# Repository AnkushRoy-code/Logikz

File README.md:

# Logikz

I designed a simple circuit board that can function as three different logic
gates:- `AND`, `OR`, and `NOR`

<p align="center">
  <br>
</p>

### Making of Logikz
This is my third PCB and this time around I wanted to know how transistors
work, and also wanted to know how logic gates work. I myself implemented the
`AND` and `OR` gates but had to look up how to do a `NOR` gate. Later I also
changed how my `OR` gate works looking at the implementation of `NOR` gate.

The first iteration would've never worked, because of absolutely no current
calculations done. Used [circuit.js](https://www.falstad.com/circuit/circuitjs.html) to fix my implementation.
Earlier it had like 5 buttons, two for `A` and `B` inputs and the rset for
choosing between the gates. But had to ditch that idea because current it
didn't work in the simulation. Now I have 9 buttons, `A` and `B` for each
gates, so total 3 `A` and 3 `B` input buttons.

Reason why the first iteration didn't work: It had something to do with
"current takes the least resistive path", it is hard to explain in text.

The simulation file is present in `~/logikz_circuitjs.txt`, you can click [this](https://www.falstad.com/circuit/circuitjs.html?ctz=CQAgjCAMB0l3BWcMBMcUHYMGZIA4UA2ATmIxAQiQUgoFMBaMMAKADdxiUQUUAWTtzCFaokH1rYo0mAhYB3QeBFLCAyAtUDM3NVE06Qew8UL6ATjwzdTIbHgG3afDHAPWQTFdgTcvozR8-PjxnbGDQ-UUgz2Ewvzj9AGdxcM8Q2gQMMwYM6QgAMwBDABskuhYUvjT-CmzYlVpC0vLKu0I8BoowBLMmkGKyioAXEBwzPXG7IXBPFGhCbHtIGn5+SEIRbEYEKXnF5dW+dYQ8HB2IMDgQABM6YoBXEuHAhxBbewE9DWi3vWrdOpXo4zJ9wChOj87G8ep0AeDIW14XoEHwvupZoNWlU0rCKGiEfkBi0KpZKL0jPwurReFDrLQGGlQgy0nS0J40vTplEQMyOdw+azNKj0WNsBMgYoML5udlOkKpR1ZUq0IjFGAuDwqRruIYoTqrNw5YaecbVWMVR4NKM8MIjAJbaCZhAGPslqEjus+L5CDs9gt3StIGsJKdiHwLshaHdHs9NI77by7cxuFCRYSE3ioZmIUmzCmeXg0ky9AreaWBXoDdmq5q8MYrfGG0bLan49dGTYevyecRu53wGBxT39UOcrix3MqRphEJJ67tSgarxtLd7kUnsMGCU6DdZmIYJBWOql34V+C0nrND1Lx569pG6NpQlu8+Gv0IBhoDfxWAEKQ4BCRYdmIcBoGOPhCGsJZhFcAEUB2TormjddNxYG07SYbsE1qS45mgGgEEIIjgz4UhhE2BAQJ4aAUFRShiNMao-xQYhqOQtdYxeRVOlqPlajTepaimASWEsQwGA+JVJL6cRXChcVeILPhMILBTpMiFSckiDQqlU7t0yw1NMRJJFMMiQydJMoZNGInICxEtT4xqRIriI98eTc+yVC8qdJWQdyFwEZhhyCnkJMSCSYg0cSPEZGVFI5GVnHk9TeJiRLGTeNKku4TLwgCaJpIK8QOxKnKsoECQWWypEyrePJKqJLEKiqMr2Ua8rrNaMkCQYSI7M8KyXDcXqBCMoxArUuS3CfUKljMESwTwphoGwOUsnCbAh0oVw8EYPRXVgf8fB6VF62EIiIwYKtrhjDc41GKC-AWow4uW2YwHAosOn4ERMDIjpfRunJCAWbIsiuDAbxwU4qJupAOPutDFE6t5-xe2rFAxjl0c1RlhzTfHXuejlCc0Tr2SW9k6Xmqn5vJ7GhLyQgqVyHTbLZsFBqaqFWfGvI4PSDmpUgcawS5XnbLwdK-hl9IyzfJqlfhPn5dyTkZQ1tspS1+ErjZ1Xr1IhWhBWHIjfVc3TYC8clRi22OSVXywppNBAmku0Ir6dxARNMt+a6UmvB5YPOXZAc6S1hzQqcxRvZpOKnF9zxbAkkIeUyqSlO7Crs6GwrJu02gcJFvMC-Lia+fe3Q4rtKF086b3wrrsxDADw2Bq5rGxjF3GBCF9nC6imVG+HuK8hiIf9CAA) link to see my project in action.

### PCB

<table>
  <tr>
    <td align="center">
      <br>
      <b>Front Of the PCB</b>
    </td>
    <td align="center">
      <br>
      <b>Back Of the PCB</b>
    </td>
    <td align="center">
      <br>
      <b>Back of the PCB without Silkscreen</b>
    </td>
  </tr>
  <tr>
    <td align="center">
      <br>
      <b>Front Of the PCB (3D)</b>
    </td>
    <td align="center">
      <br>
      <b>Back Of the PCB (3D)</b>
    </td>
    <td align="center">
      <br>
      <b>Simulation in CircuitJS</b>
    </td>
  </tr>
</table>

### SChematic
<p align="center">
  <br>
</p>

### BOM
`~/BOM.csv` has BOM of this project.

| QTY            | Name              |
| -------------- | ---------------   |
| 1              | Battery Holder    |
| 1              | LED               |
| 6              | NPN Transistor    |
| 2              | 220 Ohm Resistor  |
| 5              | 4.7k Ohm Resistor |
| 9              | Push Button       |

Made by `@Ankush Roy` in Slack from Hack Club

Made as a part of https://solder.hackclub.com/!

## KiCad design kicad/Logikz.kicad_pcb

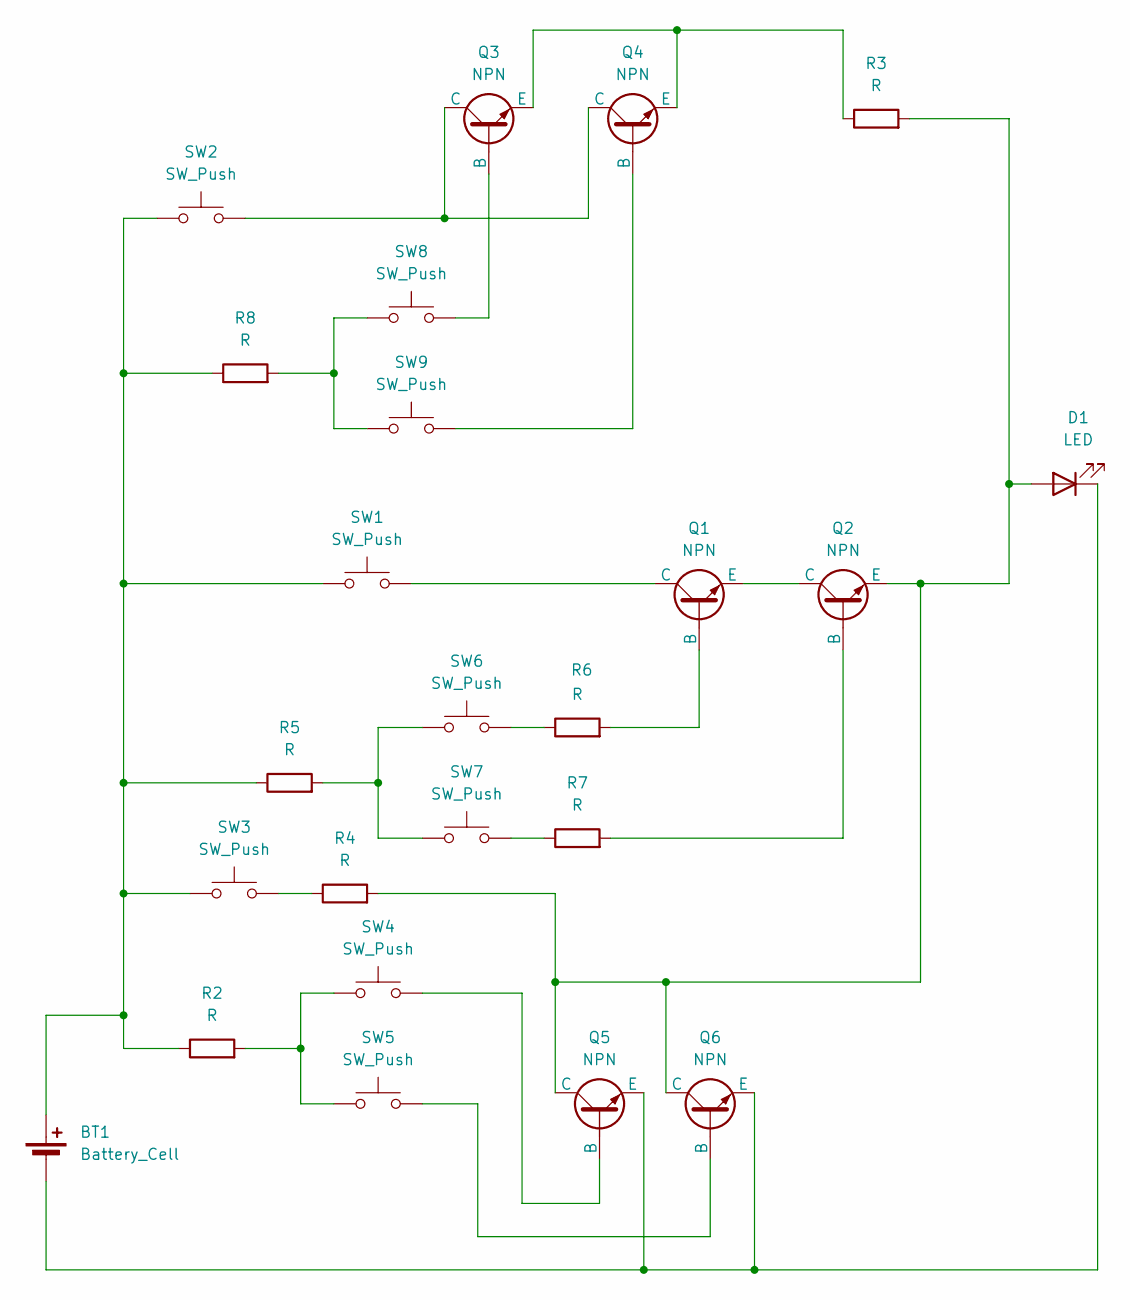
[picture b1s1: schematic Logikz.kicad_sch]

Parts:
BT1: Battery_Cell; BatteryHolder_Keystone_3034_1x20mm
D1: LED; LED_D5.0mm
Q1, Q2, Q3, Q4, Q5, Q6: NPN; TO-92L_HandSolder
R2, R3, R4, R5, R6, R7, R8: R; R_Axial_DIN0207_L6.3mm_D2.5mm_P7.62mm_Horizontal
SW1, SW2, SW3, SW4, SW5, SW6, SW7, SW8, SW9: SW_Push; SW_PUSH_6mm

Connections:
unnamed: BT1.1 (+), R2.1, R5.1, R8.1, SW1.1, SW2.1, SW3.1
unnamed: BT1.2 (-), D1.1 (K), Q5.3 (E), Q6.3 (E)
unnamed: D1.2 (A), Q2.3 (E), Q5.1 (C), Q6.1 (C), R3.2, R4.2
unnamed: Q1.2 (B), R6.2
unnamed: Q1.1 (C), SW1.2
unnamed: Q1.3 (E), Q2.1 (C)
unnamed: Q2.2 (B), R7.2
unnamed: Q3.2 (B), SW8.2
unnamed: Q3.1 (C), Q4.1 (C), SW2.2
unnamed: Q3.3 (E), Q4.3 (E), R3.1
unnamed: Q4.2 (B), SW9.2
unnamed: Q5.2 (B), SW4.2
unnamed: Q6.2 (B), SW5.2
unnamed: R2.2, SW4.1, SW5.1
unnamed: R4.1, SW3.2
unnamed: R5.2, SW6.1, SW7.1
unnamed: R6.1, SW6.2
unnamed: R7.1, SW7.2
unnamed: R8.2, SW8.1, SW9.1

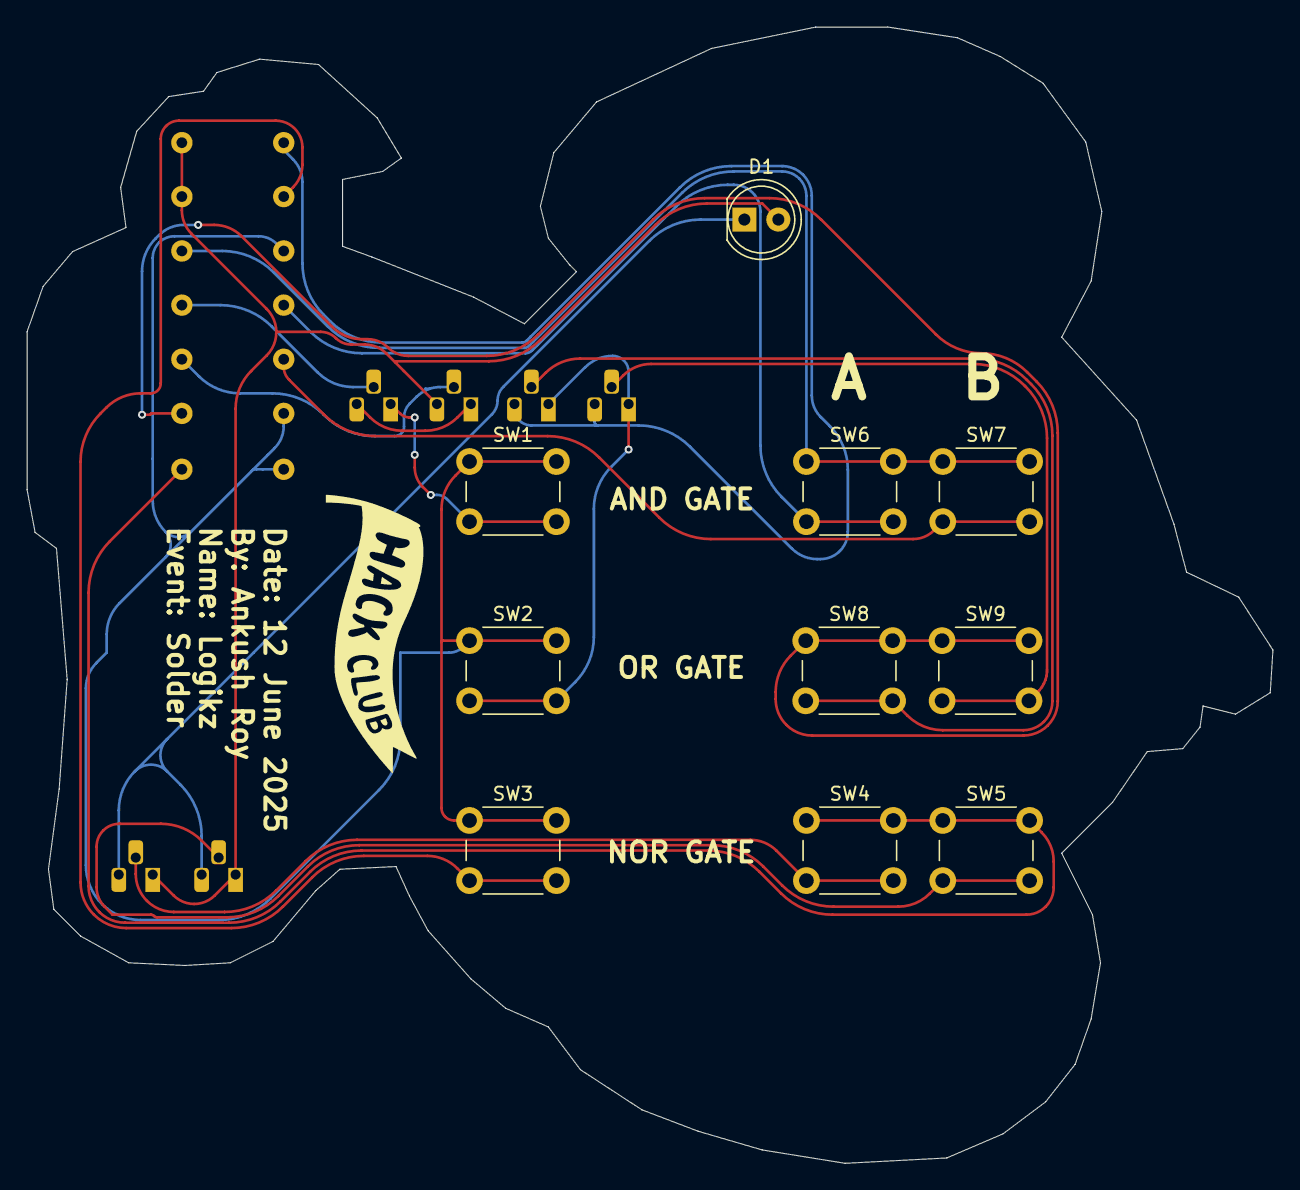
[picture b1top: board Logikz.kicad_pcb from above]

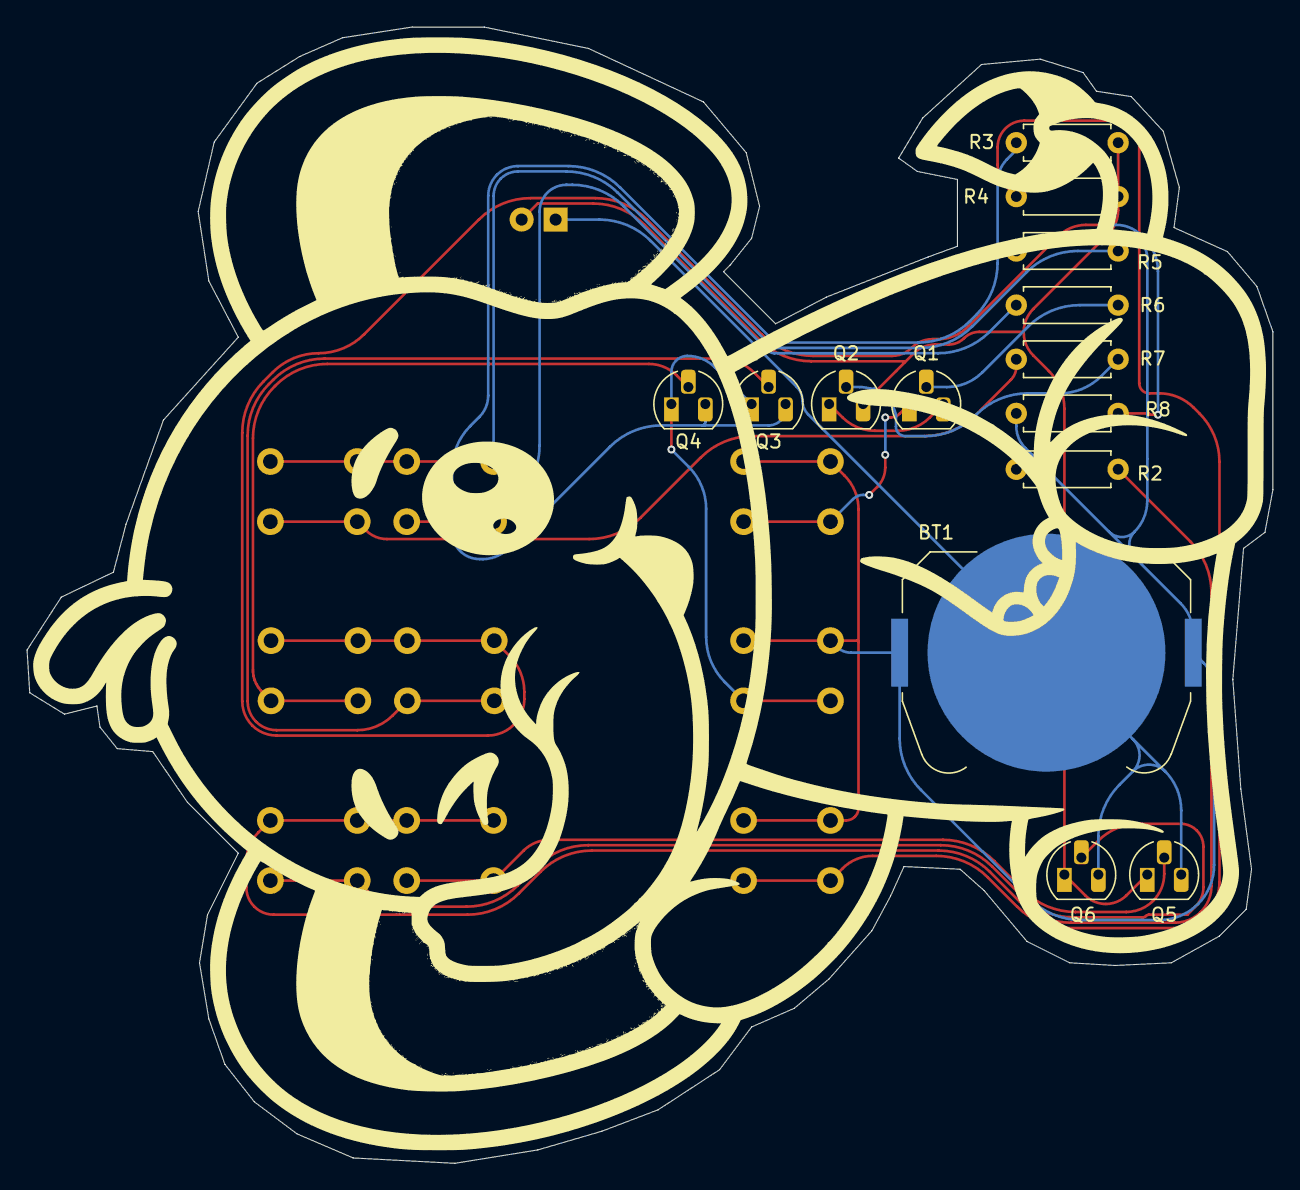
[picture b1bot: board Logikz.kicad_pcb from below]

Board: 2 copper layers, 93.2 x 85.0 mm, 24 parts (14 on the bottom side), 19 nets.

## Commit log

2025-06-12 batman
2025-06-12 silkscreens to the pcb
2025-06-12 added readme text
2025-06-12 added images
2025-07-04 Changed the wires to roundedgit add!! Looks very cool!
